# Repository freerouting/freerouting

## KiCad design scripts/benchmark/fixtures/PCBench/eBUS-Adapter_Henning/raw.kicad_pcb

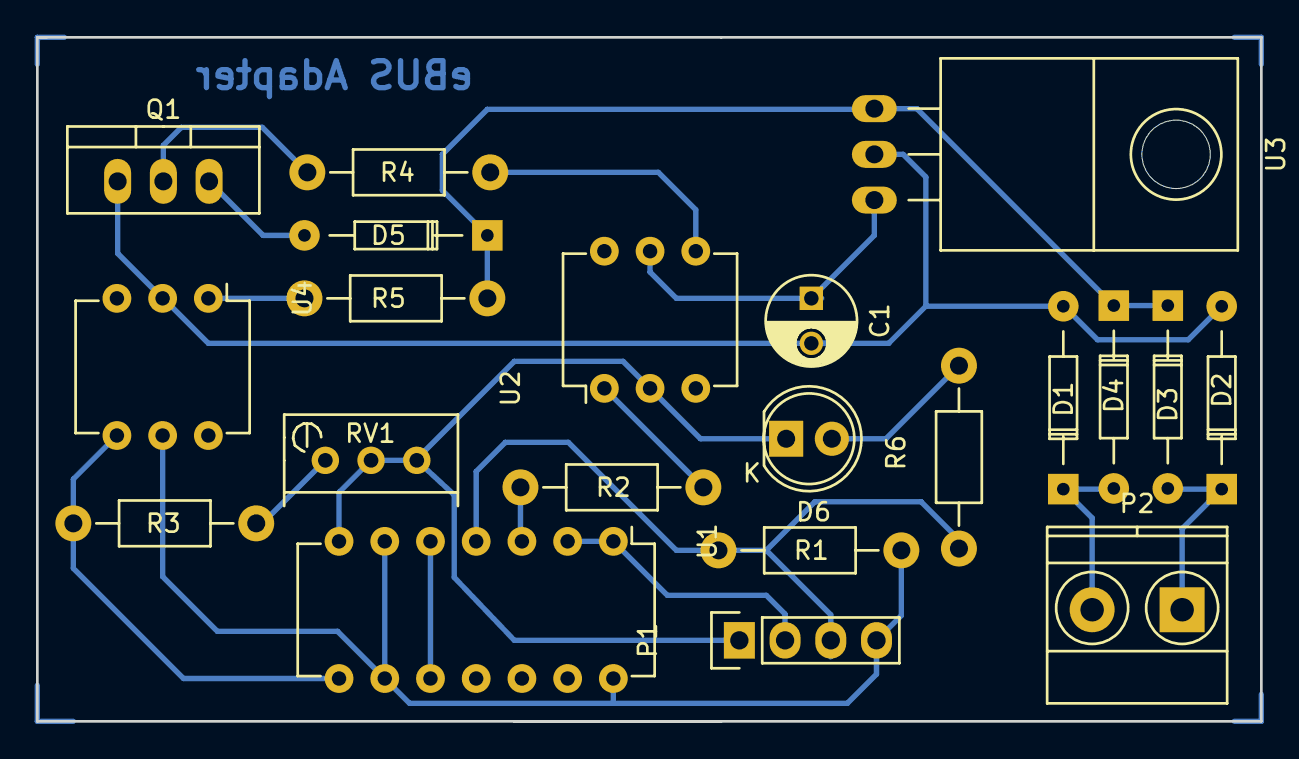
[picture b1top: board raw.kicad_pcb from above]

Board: 2 copper layers, 68.0 x 38.0 mm, 21 parts (0 on the bottom side), 19 nets.

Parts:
C1: CP; C_Radial_D5_L6_P2.5
D1, D2, D3, D4: 1N4148; Diode_DO-35_SOD27_Horizontal_RM10
D5: ZPY7.5V 1.3W; Diode_DO-35_SOD27_Horizontal_RM10
D6: LED; LED-5MM
P1: RS232; Pin_Header_Straight_1x04
P2: EBUS; TerminalBlock_Pheonix_MKDS1.5-2pol
Q1: BD645; TO-220_Neutral123_Vertical
R1: 10k; Resistor_Horizontal_RM10mm
R2: 470; Resistor_Horizontal_RM10mm
R3, R6: 1k; Resistor_Horizontal_RM10mm
R4: 22k; Resistor_Horizontal_RM10mm
R5: 3k3; Resistor_Horizontal_RM10mm
RV1: 20k; Potentiometer_Bourns_3296W_3-8Zoll_Inline_ScrewUp
U1: 4011; DIP-14_W7.62mm
U2, U4: CNY17-1; DIP-6_W7.62mm
U3: 78L05; TO-220_Neutral123_Horizontal

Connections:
EBUS1: D1.1, D4.2, P2.2
EBUS2: D2.1, D3.2, P2.1
GND: D6.1, P1.1, RV1.2, RV1.3, U1.7, U2.2
unnamed: C1.1, U2.5, U3.3
unnamed: C1.2, D1.2, D2.2, Q1.1, U3.2, U4.2
unnamed: D3.1, D4.1, D5.1, R5.1, U3.1
unnamed: D5.2, Q1.3
unnamed: D6.2, R6.2
unnamed: Q1.2, R4.1
unnamed: R2.1, U2.1
unnamed: R2.2, U1.3
unnamed: R3.1, U1.8, U4.4
unnamed: R3.2, RV1.1
unnamed: R4.2, U2.4
unnamed: R5.2, U4.1
unnamed: U1.5, U1.10
RXD: P1.3, R1.2, R6.1, U1.4
TXD: P1.2, U1.1, U1.2
VDD: P1.4, R1.1, U1.6, U1.9, U1.14, U4.5

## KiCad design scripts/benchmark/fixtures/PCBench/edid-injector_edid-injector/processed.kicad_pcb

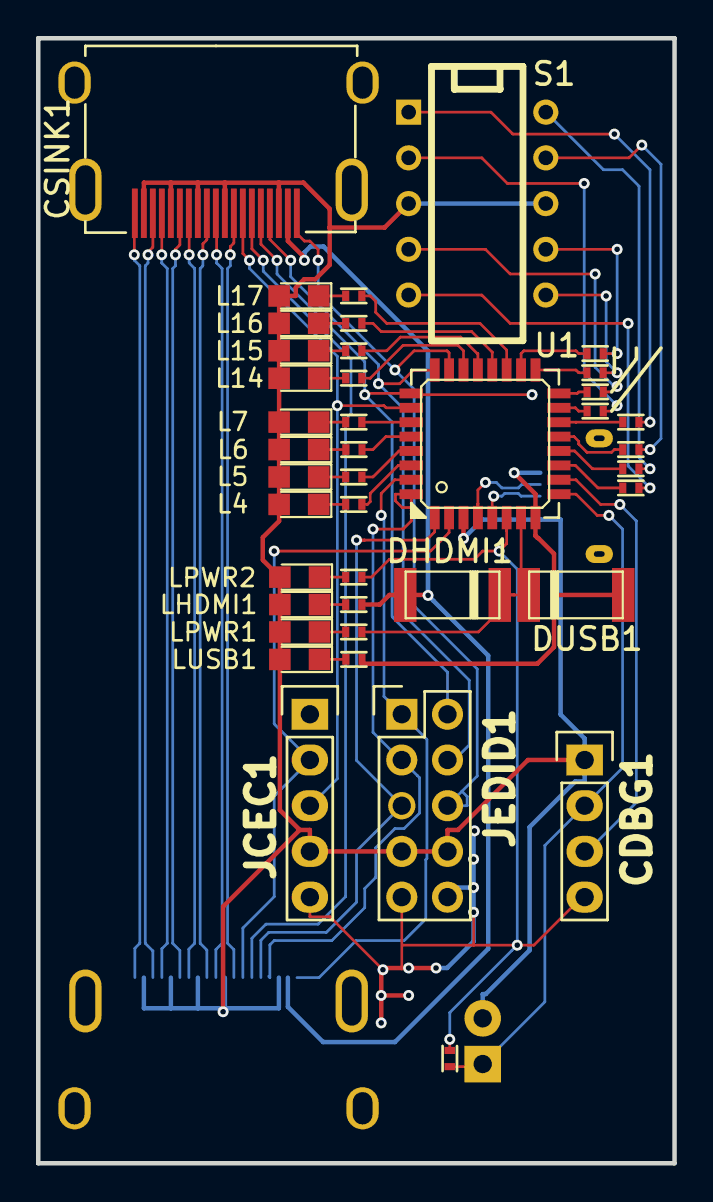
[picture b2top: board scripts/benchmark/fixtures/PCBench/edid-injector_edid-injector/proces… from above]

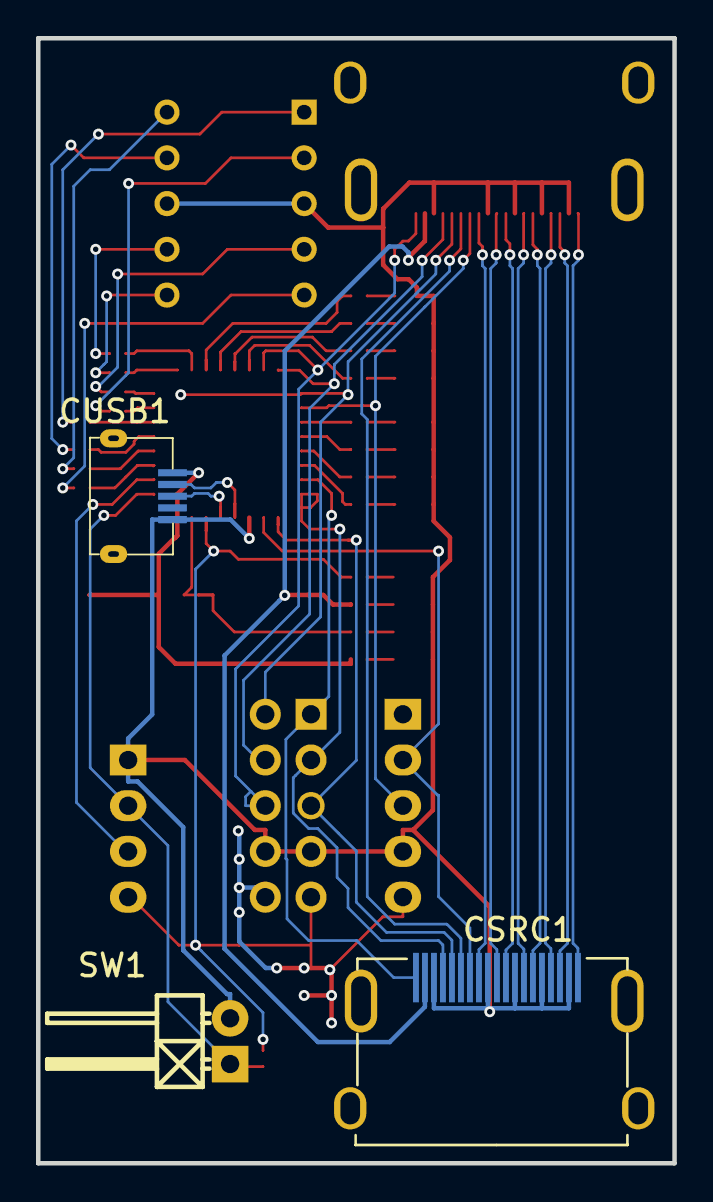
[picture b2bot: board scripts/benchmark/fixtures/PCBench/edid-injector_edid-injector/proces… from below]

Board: 2 copper layers, 35.3 x 62.5 mm, 44 parts (3 on the bottom side), 62 nets.

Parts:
CDBG1: CONN_01X04; Pin_Header_Straight_1x04
CSINK1: HDMI; hdmi
CSRC1: HDMI; hdmi
CUSB1: USB-MINI-B2; micro-usb
DHDMI1: DIODE; sod323
DUSB1: DIODE; sod323
JCEC1: CONN_01X05; Pin_Header_Straight_1x05
JEDID1: CONN_02X05; Pin_Header_Straight_2x05
L4, L5, L6, L7, L14, L15, L16, L17: LED; LED_0805
LHDMI1: LED; LED_0805
LPWR1, LPWR2: LED; LED_0805
LUSB1: LED; LED_0805
RHDMI1: R; R_0402
RL4, RL5, RL6, RL7, RL14, RL15, RL16, RL17: R; R_0402
RPWR1, RPWR2: R; R_0402
RRST1: R; R_0402
RSEGA1: R; R_0402
RSEGB1: R; R_0402
RSEGC1: R; R_0402
RSEGD1: R; R_0402
RSEGE1: R; R_0402
RSEGF1: R; R_0402
RSEGG1: R; R_0402
RSEGP1: R; R_0402
RUSB1: R; R_0402
S1: 7SEGM; DIP-10__300
SW1: SW_PUSH; Pin_Header_Angled_1x02
U1: C8051F381/3/5/7/C-GQ; lqfp32

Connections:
/CLK+: CSINK1.10, CSRC1.10
/CLK-: CSINK1.12, CSRC1.12
/D0+: CSINK1.7, CSRC1.7
/D0-: CSINK1.9, CSRC1.9
/D1+: CSINK1.4, CSRC1.4
/D1-: CSINK1.6, CSRC1.6
/D2+: CSINK1.1, CSRC1.1
/D2-: CSINK1.3, CSRC1.3
/D+: CUSB1.2, U1.4
/D-: CUSB1.3, U1.5
/RES: CSINK1.14, CSRC1.14
/SINK_CEC: CSINK1.13, JCEC1.3, U1.26
/SINK_HPD: CSINK1.19, JEDID1.6, U1.23
/SINK_SCL: CSINK1.15, JEDID1.2, U1.25
/SINK_SDA: CSINK1.16, JEDID1.4, U1.24
/SRC_CEC: CSRC1.13, JCEC1.2, U1.2
/SRC_HPD: CSRC1.19, JEDID1.1, U1.31
/SRC_SCL: CSRC1.15, JEDID1.5, U1.1
/SRC_SDA: CSRC1.16, JEDID1.3, U1.32
/VCC3V3: CDBG1.4, JCEC1.5, JEDID1.9, JEDID1.10, RPWR2.2, RRST1.2, U1.6
/VCC5V0: DHDMI1.2, DUSB1.2, RPWR1.1, U1.7
/VHDMI: CSINK1.18, CSRC1.18, DHDMI1.1, RHDMI1.2
/VUSB: CUSB1.1, DUSB1.1, RUSB1.2, U1.8
GND: CDBG1.1, CSINK1.2, CSINK1.5, CSINK1.8, CSINK1.11, CSINK1.17, CSRC1.2, CSRC1.5, CSRC1.8, CSRC1.11, CSRC1.17, CUSB1.5, JCEC1.4, JEDID1.7, JEDID1.8, L4.2, L5.2, L6.2, L7.2, L14.2, L15.2, L16.2, L17.2, LHDMI1.2, LPWR1.2, LPWR2.2, LUSB1.2, S1.3, S1.8, SW1.2, U1.3
unnamed: CDBG1.2, RRST1.1, SW1.1, U1.9
unnamed: CDBG1.3, U1.10
unnamed: L4.1, RL4.2
unnamed: L5.1, RL5.2
unnamed: L6.1, RL6.2
unnamed: L7.1, RL7.2
unnamed: L14.1, RL14.2
unnamed: L15.1, RL15.2
unnamed: L16.1, RL16.2
unnamed: L17.1, RL17.2
unnamed: LHDMI1.1, RHDMI1.1
unnamed: LPWR1.1, RPWR1.2
unnamed: LPWR2.1, RPWR2.1
unnamed: LUSB1.1, RUSB1.1
unnamed: RL4.1, U1.30
unnamed: RL5.1, U1.29
unnamed: RL6.1, U1.28
unnamed: RL7.1, U1.27
unnamed: RL14.1, U1.22
unnamed: RL15.1, U1.21
unnamed: RL16.1, U1.20
unnamed: RL17.1, U1.19
unnamed: RSEGA1.1, U1.18
unnamed: RSEGA1.2, S1.7
unnamed: RSEGB1.1, U1.17
unnamed: RSEGB1.2, S1.6
unnamed: RSEGC1.1, U1.16
unnamed: RSEGC1.2, S1.4
unnamed: RSEGD1.1, U1.15
unnamed: RSEGD1.2, S1.2
unnamed: RSEGE1.1, U1.14
unnamed: RSEGE1.2, S1.1
unnamed: RSEGF1.1, U1.13
unnamed: RSEGF1.2, S1.9
unnamed: RSEGG1.1, U1.12
unnamed: RSEGG1.2, S1.10
unnamed: RSEGP1.1, U1.11
unnamed: RSEGP1.2, S1.5

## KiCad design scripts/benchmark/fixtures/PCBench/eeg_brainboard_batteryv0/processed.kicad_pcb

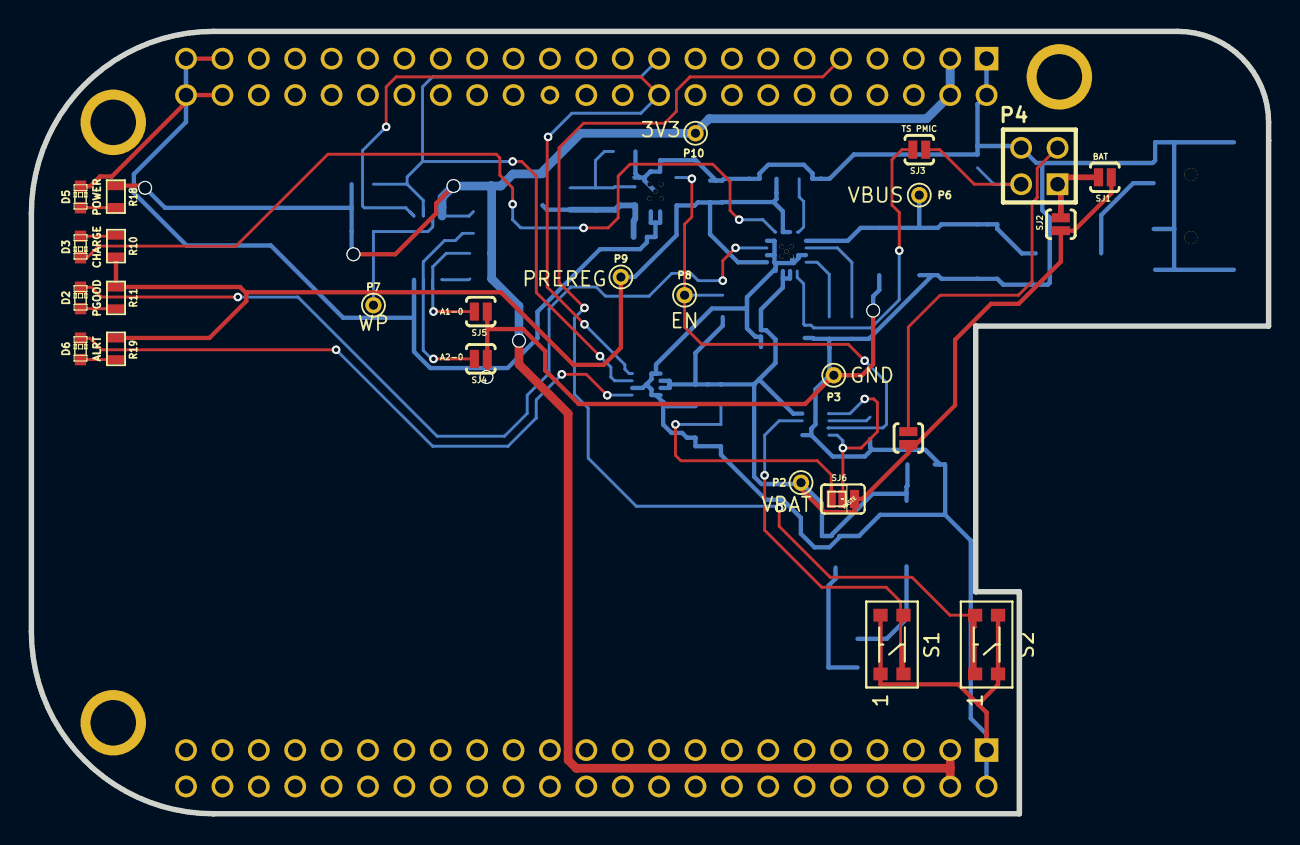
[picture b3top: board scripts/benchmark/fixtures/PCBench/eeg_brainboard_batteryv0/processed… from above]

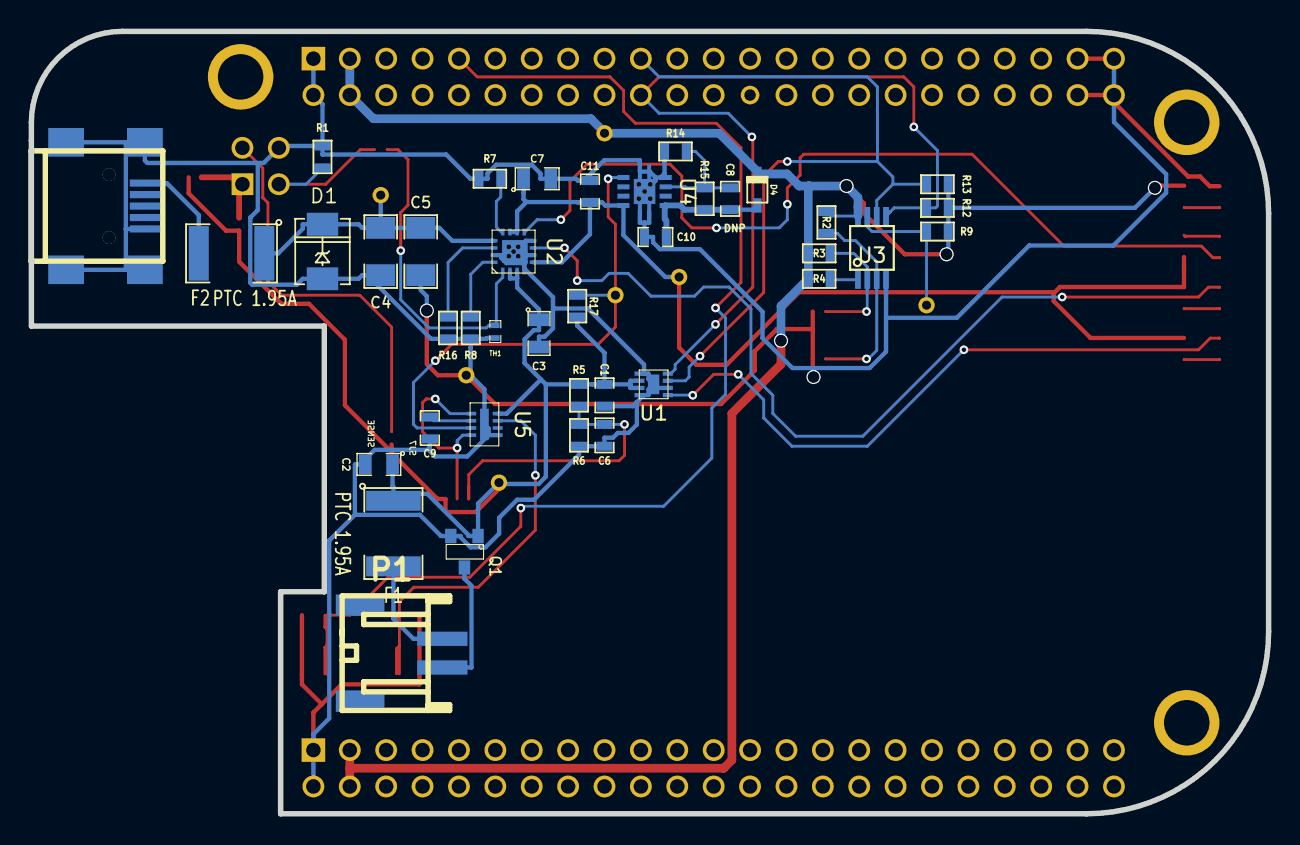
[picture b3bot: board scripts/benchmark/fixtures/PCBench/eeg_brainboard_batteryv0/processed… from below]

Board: 2 copper layers, 86.4 x 54.6 mm, 65 parts (39 on the bottom side), 36 nets.

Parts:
C1, C11: 0.1uF; SM0603_Capa
C2, C3, C7: 10uF; SM0805
C4, C5: 10uF; SM1206
C6, C8: 0.01uF; SM0603_Capa
C9: 0.47uF; SM0603_Capa
C10: 2.2uF; SM0603_Capa
CON1: USB-MINI-B; USB_MINI_B
D1: SMAJ7.0A; DO-214AC(SMA)
D2: PGOOD; LED-0603
D3: CHARGE; LED-0603
D4: PMEG2005AEA; sod323
D5: POWER; LED-0603
D6: ALRT; LED-0603
F1, F2: PTC 1.95A; SM1812
P1: JST; s2b-ph-sm4-tb
P2: VBAT; PINTST
P3: GND; PINTST
P4: BBB_PMIC; PIN_ARRAY_2X2
P6: VBUS; PINTST
P7: WP; PINTST
P8: EN; PINTST
P9: PREREG; PINTST
P10: 3V3; PINTST
Q1: SI2312; SOT23
R1: 75k; SM0603
R2, R3, R4: 4.7k; SM0603
R5, R17: 806k; SM0603
R6: 191k; SM0603
R7: 1.18k; SM0603
R8, R10, R11, R18, R19: 2.2k; SM0603
R9: 10k; SM0603
R12, R13: 5.6k; SM0603
R14: 30.1k; SM0603
R15, R16: 52.3k; SM0603
S1: SYSOFF; KMR231GLFS
S2: BBB_SLEEP; KMR231GLFS
SJ1, SJ2: BAT; SparkFun-Passives-SJ_2S-NO
SJ3: TS PMIC; SparkFun-Passives-SJ_2S-NO
SJ4: A2-0; SparkFun-Passives-SJ_2S-NO
SJ5: A1-0; SparkFun-Passives-SJ_2S-NO
SJ6: LOWBAT_DIS; SparkFun-Passives-SJ_3_PASTE1&2
SJ7: SENSE; SparkFun-Passives-SJ_2S-NO
TH1: NTC 10K; SM0402
U1: MAX17048; tdfn8-2x2
U2: BQ24074(T); s-pvqfn-n16-vias
U3: 24C256; SSOP8
U4: TPS73601-SON; s-pvson-n8-vias
U5: LTC2951-1; dfn8-3x2
U6: BEAGLEBONE_BLACK; BEAGLEBONE_BLACK_BATTMOD

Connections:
+3.3V: D4.2, P10.1, R2.1, R3.1, R4.1, R9.1, R12.1, R13.1, R18.2, U3.8, U6.A3, U6.A4, U6.B3, U6.B4
+BATT: C1.1, C2.1, C3.1, F1.1, P2.1, Q1.1, R5.1, R17.1, SJ1.1, SJ2.1, SJ6.3, SJ7.1, U1.2, U1.3, U2.2, U2.3, U5.4
/A0: R4.2, U3.1
/A1: R3.2, SJ5.2, U3.2
/A2: R2.2, SJ4.2, U3.3
/B+: F1.2, P1.1
/B-: P1.2, Q1.3
/BAT: P4.1, SJ1.2, SJ2.2
/BBB_TS: P4.2, R1.1, SJ3.1
/EN: P8.1, R17.2, U4.5, U5.7
/FB: C8.2, R14.2, R15.2, U4.3
/ILIM: R7.2, U2.12
/ISET: R8.1, U2.16
/LOWBAT: C6.1, R5.2, R6.1, SJ6.1
/OFFT: C9.1, U5.6
/OUT: C7.1, C11.1, P9.1, R10.1, R11.1, R19.1, U2.5, U2.10, U2.11, U4.8
/PWR_BUT: S2.1, S2.3, U6.B9
/REGOUT: C8.1, C10.1, D4.1, R15.1, U4.1
/SCL: R13.2, U1.7, U3.6, U6.B19
/SDA: R12.2, U1.8, U3.5, U6.B20
/SENSE: P4.3, SJ7.2
/TMR: R16.1, U2.14
/TS: SJ3.2, TH1.1, U2.1
/VBUS: C4.1, C5.1, D1.2, F2.1, P6.1, U2.13
/VIN: CON1.1, F2.2
/WP: P7.1, R9.2, U3.7
/~ALRT: D6.2, U1.5
/~CHG: D3.2, U2.9
/~KILL: SJ6.2, U5.5, U5.8
/~PB: S1.2, S1.4, U5.3
/~PGOOD: D2.2, U2.7
GND: C1.2, C2.2, C3.2, C4.2, C5.2, C6.2, C7.2, C9.2, C10.2, C11.2, CON1.5, CON1.6, CON1.7, CON1.8, CON1.9, D1.1, D5.2, P3.1, P4.4, Q1.2, R1.2, R6.2, R7.1, R8.2, R14.1, R16.2, S1.1, S1.3, S2.2, S2.4, SJ4.1, SJ5.1, TH1.2, U1.1, U1.4, U1.6, U1.9, U2.4, U2.6, U2.8, U2.15, U2.17, U3.4, U4.4, U4.9, U5.1, U5.9, U6.A1, U6.A2, U6.B1, U6.B2, U6.B43, U6.B44, U6.B45, U6.B46
unnamed: D3.1, R10.2
unnamed: D2.1, R11.2
unnamed: D5.1, R18.1
unnamed: D6.1, R19.2
